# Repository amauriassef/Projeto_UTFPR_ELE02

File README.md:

- [1. Projeto UTFPR ELE02](#1-Projeto-UTFPR-ELE02)
   * [1.1 Universidade Tecnológica Federal do Paraná](#11-Universidade-Tecnológica-Federal-do-Paraná)
   * [1.2 Título](#12-Título)
   * [1.3 Descrição](#13-Descrição)
   * [1.4 Equipe](#14-Equipe)
   * [1.5 Documentação](#15-Documentação)
     + [1.5.1 Características](#151-Características)
     + [1.5.2 Versão do projeto](#152-Versão-do-projeto)
     + [1.5.3 Histórico de versão](#153-Histórico-de-versão)
     + [1.5.4 Informações para fabricação da placa](#154-Informações-para-fabricação-da-placa)
   * [1.6 Pinagem do kit](#16-Pinagem-do-kit)
     + [1.6.1 Descrição dos sinais da placa MICROTB_UTFPR](#161-Descrição-dos-sinais-da-placa-MICROTB_UTFPR)
     + [1.6.2 Descrição dos sinais por funcionalidade](#162-Descrição-dos-sinais-por-funcionalidade) 
        + [1.6.2.1 LEDs](#1621-LEDs) 
        + [1.6.2.2 Chaves push-button](#1622-Chaves-push-button) 
        + [1.6.2.3 Displays de 7 segmentos multiplexados](#1623-Displays-de-7-segmentos-multiplexados) 
        + [1.6.2.4 Display LCD 16x2](#1624-Display-LCD-16x2)
        + [1.6.2.5 Motor de passo e servomotor](#1625-Motor-de-passo-e-servomotor)
        + [1.6.2.6 Módulo sensor de ultrassom HC-04](#1626-Módulo-sensor-de-ultrassom-HC-04)
        + [1.6.2.7 Módulo Bluetooth HC-05 ou HC-06](#1627-Módulo-Bluetooth-HC-05-ou-HC-06)
        + [1.6.2.8 Módulo WiFi ESP8266](#1628-Módulo-WiFi-ESP8266)
        + [1.6.2.9 Módulo I2C sensor de pressão BMP280](#1629-Módulo-I2C-sensor-de-pressão-BMP280)
        + [1.6.2.10 Sinais analógicos](#16210-Sinais-analógicos)
        + [1.6.2.11 Jumpers](#16211-Jumpers)
        + [1.6.2.12 Conectores](#16212-Conectores)
        + [1.6.2.13 Sinais não conectados da placa Tiva LaunchPad](#16213-Sinais-não-conectados-da-placa-Tiva-LaunchPad)
        + [1.6.2.14 Sinais não conectados da placa Blue Pill](#16214-Sinais-não-conectados-da-placa-Blue-Pill)
- [2. Links com informações sobre as placas de avaliação compatíveis](#2-Links-com-informações-sobre-as-placas-de-avaliação-compatíveis)
   * [2.1 Placa TIVA C Series TM4C123G LaunchPad](#21-placa-TIVA-C-Series-TM4C123G-LaunchPad)
     + [2.1.1 Links do professor Jonathan W Valvano](#211-Links-do-professor-Jonathan-W-Valvano)
   * [2.2 Placa Blue Pill](#22-placa-Blue-Pill)
   * [2.3 Placa Black Pill](#23-placa-Black-Pill)
- [3. Site para download do software Eagle](#3-Site-para-download-do-software-Eagle)
- [4. Site do projeto](#4-Site-do-projeto)  
- [5. Como citar este trabalho](#5-Como-citar-este-trabalho)  
- [6. Informação de licença](#6-Informação-de-licença)  

# 1. Projeto UTFPR ELE02 

## 1.1 Universidade Tecnológica Federal do Paraná

* Departamento Acadêmico de Eletrotécnica (DAELT) - Campus Curitiba
* Departamento Acadêmico de Eletrônica (DAELN) - Campus Curitiba
* Departamento de Eletrônica (DAELE) - Campus Ponta Grossa
* Link: http://www.utfpr.edu.br/

## 1.2 Título 

Desenvolvimento de um kit microcontrolado de baixo custo para apoio ao ensino remoto - Projeto ELE02 
 
## 1.3 Descrição 

Projeto do circuito esquemático e *layout* da placa de circuito impresso (PCB) **MICROTB_UTFPR** utilizando o software [Eagle 9.6.2](https://www.autodesk.com/products/eagle/). A placa **MICROTB_UTFPR** permite conexão com a placa TIVA™ C Series TM4C123G LaunchPad ou Blue-Pill para aplicações de Sistemas Microcontrolados envolvendo automação, controle e IoT, entre outras.

Projeto aprovado no [Edital 37/2020 PROGRAD – UTFPR – Área temática de Sistemas Microcontrolados](http://portal.utfpr.edu.br/editais/graduacao-e-educacao-profissional/reitoria/edital-37-2020-prograd) como apoio no desenvolvimento dos Recursos Educacionais Abertos (REA).

Para fins do Edital 37/2020, entende-se que Recursos Educacionais Abertos (REA) “são materiais de aprendizado, ensino e pesquisa em qualquer formato e mídia de domínio público ou com direitos autorais liberados sob uma licença aberta, que permitem acesso, reutilização sem custo, adaptação e redistribuição gratuita” [(UNESCO, 2019)](http://www.unesco.org/new/fileadmin/MULTIMEDIA/HQ/CI/CI/pdf/publications/oer_guidelines_pt.pdf).

## 1.4 Equipe 
 
* Amauri Amorin Assef – Coordenador – http://lattes.cnpq.br/0720172921923496
* Guilherme Luiz Moritz – Colaborador – http://lattes.cnpq.br/0736175449254807
* Delvanei Gomes Bandeira Junior – Colaborador – http://lattes.cnpq.br/2233204054325472
* Guilherme de Santi Peron – Colaborador –  http://lattes.cnpq.br/7845448730478685
* Maurício dos Santos Kaster – Colaborador – http://lattes.cnpq.br/5494434934031784
* Murilo Paulo de Oliveira – Bolsista – http://lattes.cnpq.br/1578999659029568
* Cáled Tarique Pereira – Voluntário – http://lattes.cnpq.br/5596843081337675
 
## 1.5 Documentação

* [**BOM_MICROTB**](/BOM_MICROTB) - Lista de material (*bill of material*) da placa MICROTB_UTFPR.
* [**CAD_EAGLE_9_6_2_MICROTB**](/CAD_EAGLE_9_6_2_MICROTB) - Projeto do circuito esquemático e *layout* da placa MICROTB_UTFPR.
* [**LIB_MICROTB**](/LIB_MICROTB) - Biblioteca com os componentes do circuito esquemático e placa MICROTB_UTFPR.
* [**PDF_MICROTB**](/PDF_MICROTB) - Arquivos em formato PDF para visualização do circuito esquemático e projeto da placa.

Obs: após abrir o arquivo da placa (board) no software Autodesk Eagle versão 9.6.2 (© 2020 Autodesk, Inc.), clicar em **Ratsnest** para mostrar os planos de GND dos layers *top* e *bottom*.

### 1.5.1 Características

* Permite conexão com as placas TIVA™ C Series TM4C123G LaunchPad e Blue Pill
* 2 displays de 7 segmentos tipo catodo comum multiplexados
* 8 LEDs para controle lógico visual
* Sensor de temperatura LM35
* Potenciômetro para leitura analógica
* Driver ponte-H dupla L293D para controle de motor de passo e CC
* Conector para módulo WiFi ESP8266
* Conector para módulo Bluetooth HC-05/06
* Conector para controle de micro servomotor de 3 fios com sinal PWM
* Conector para módulo sensor ultrassônico HC-04
* Conector para módulo sensor de sensor de pressão BMP280
* Display alfanumérico LCD 16x2 no modo de 4 bits
* Alimentação pela USB ou fonte externa de 9 V/1 A com conector do tipo P4 (2,5 x 5,5 mm)

### 1.5.2 Versão do projeto

**MICROTB_UTFPR V1.0** - Versão inicial do projeto

### 1.5.3 Histórico de versão 

**V1.0** - Versão inicial da placa MICROTB_UTFPR 

### 1.5.4 Informações para fabricação da placa

* Material: Dupla face FR4
* Dimensão da placa: 100 x 80 (mm2)
* Espessura da PCI: 1,60 mm
* Acabamento Superficial: HAL (Sn/Pb)
* Espessura final do cobre externo (Base + Plating): 1.0oz
* Cor da máscara de solda (top): Verde
* Cor da máscara de componentes (top): Branca
* Menor pista: 0,28 mm (11 mil)
* Menor isolação: 0,305 mm (12 mil)

## 1.6 Pinagem do kit

### 1.6.1. Descrição dos sinais da placa MICROTB_UTFPR

|Conector TIVA|	Pino do conector M1 (Tiva)|	Sinal Tiva|	Pino do conector M2 (Blue Pill)|	Sinal Blue Pill|	Sinal Black Pill |Nome do sinal final|	Interface  |	Direção    |
|:---:        |:---:                      |:---:      |:---:                           |:---:            |:---:              |:---:              |:---:        |:---:        |
|J1-1	        |1                          |	3,3 V     |	18, 21                         |	3,3 V          |	3,3 V            |	+3V3(TB)         |	Alimentação|	Alimentação|
|J1-2         |3                          |	PB5       |	10                             |	PA5            |	PA6              |	PB5_PA5          |	LED6, SEG_F e LCD_D5       | OUT    |  
|J1-3       	|5	                        |PB0	      |5	                             |PA0	|NRST	|PB0_PA0	|LED1 e SEG_A|	OUT/NC|
|J1-4	|7	|PB1	|6	|PA1	|PA0  |PB1_PA1	|LED2 e SEG_B|	OUT|
|J1-5	|9	|PE4	|16	|PB11	|PB2 |PE4_PB11	|ESP_TX, BLUETOOTH_TX e BMP280	|IN|
|J1-6	|11	|PE5	|15	|PB10	|PB1 |PE5_PB10	|ESP_RX, BLUETOOTH_RX e BMP280	|OUT|
|J1-7	|13	|PB4	|6	|PA4 |PA3	|PB4_PA4	|LED5, SEG_E e LCD_D4	|OUT|
|J1-8	|15	|PA5	|34	|PA10 |PA10	|PA5_PA10	|EN_DISP1	|OUT|
|J1-9	|17	|PA6	|31	|PA15 |PA15	|PA6_PA15	|EN_DISP2	|OUT|
|J1-10	|19	|PA7| PA6|	-|	-	|	-	|-|	-	|NC|
|J2-1	|22	|GND	|19, 22|	GND	|	GND |GND	|Alimentação	|Alimentação|
|J2-2	|24	|PB2	|7	|PA2	|PA1 |PB2_PA2	|LED3 e SEG_C|	OUT|
|J2-3	|26	|PE0	|29	|PB4	|PB4 |PE0_PB4	|ESP_GPIO02	|IN/OUT|
|J2-4	|28	|PF0	|24	|PB9	|PB9 |PF0_PB9	|SW2	|IN|
|J2-5	|30	|RESET	|-	|-	 |-	|-	|-	|NC
|J2-6	|32	|PB7/PD1	|12	|PA7	|PA6 |PB7_PA7	|LED8, SEG_DP e LCD_D7	|OUT|
|J2-7	|34	|PB6/PD0	|11	|PA6	|PA5 |PB6_PA6	|LED7, SEG_G e LCD_D6	|OUT|
|J2-8	|36	|PA4	|28	|PB5	|PB5 |PA4_PB5	|EN_LEDS	|OUT|
|J2-9	|38	|PA3	|40	|PB12	|PB12 |PA3_PB12	|LCD_EN	|OUT|
|J2-10	|40	|PA2	|39	|PB13	|PB13 |PA2_PB13	|LCD_RS	|OUT|
|J3-1	|2	|5,0 V	|23	|5,0 V	|5,0 V |+5V(TB)	|Alimentação	|Alimentação|
|J3-2	|4	|GND	|19, 22	|GND	|GND |GND	|Alimentação	|Alimentação|
|J3-3	|6	|PD0/PB6	|-	|-	|-	|-	|-	|NC|
|J3-4	|8	|PD1/PB7	|-	|-	|-	|-	|-	|NC|
|J3-5	|10	|PD2	|36	|PA8	|PA8 |PD2_PA8	|L293D_M3	|OUT|
|J3-6	|12	|PD3	|35	|PA9	|PA9 |PD3_PA9	|L293D_M4	|OUT|
|J3-7	|14	|PE1	|30	|PB3	|PB3 |PE1_PB3	|ESP_RST	| OUT|
|J3-8	|16	|PE2	|14	|PB1	|PB0 |PE2_PB1	|LM35	|IN (ADC)|
|J3-9	|18	|PE3	|13	|PB0	|PA7 |PE3_PB0	|Trimpot	|IN (ADC)|
|J3-10	|20	|PF1	|2	|PC13	|PC13 |PF1_PC13	|US_TRIGGER	|OUT|
|J4-1	|21	|PF2	|-	|-	|-	|-	|NC|
|J4-2	|23	|PF3	|-	|-	|-	|-	|NC|
|J4-3	|25	|PB3	|8	|PA3	|PA2 |PB3_PA3	|LED4 e SEG_D	|OUT|
|J4-4	|27	|PC4	|27|	PB6	|	PB6 |PC4_PB6	|US_ECO	|IN|
|J4-5	|29	|PC5	|26	|PB7	|PB7 |PC5_PB7	|SERVO e L293D_EN	|OUT (PWM)|
|J4-6	|31	|PC6	|38	|PB14 |PB14	|PC6_PB14	|L293D_M1	|OUT|
|J4-7	|33	|PC7	|37	|PB15	|PB15 |PC7_PB15	|L293D_M2	|OUT|
|J4-8	|35	|PD6	|-	|-	|-	|-	|-	|NC|
|J4-9	|37	|PD7	|-	|-	|-	|-	|-	|NC|
|J4-10	|39	|PF4	|25	|PB8	|PB8 |PF4_PB8	|SW1	|IN|

NC - não conectado. 

### 1.6.2. Descrição dos sinais por funcionalidade

#### 1.6.2.1 LEDs

|Conector TIVA|	Pino do conector M1 (Tiva)|	Sinal Tiva|	Pino do conector M2 (Blue Pill)|	Sinal Blue Pill|	Sinal Black Pill | Nome do sinal final|	Interface  |	Direção    |
|:---:        |:---:                      |:---:      |:---:                          |:---:          |:---:           |:---:      |:---:        |:---:        |
|J2-8	|36	|PA4	|28	|PB5	|PB5 |PA4_PB5	|EN_LEDS	|OUT|
|J1-3	|5	|PB0	|5	|PA0	|NRST |PB0_PA0	|LED1	|OUT/NC|
|J1-4	|7	|PB1	|6	|PA1	|PA0 |PB1_PA1	|LED2	|OUT|
|J2-2	|24	|PB2	|7	|PA2	|PA1 |PB2_PA2	|LED3	|OUT|
|J4-3	|25	|PB3	|8	|PA3	|PA2 |PB3_PA3	|LED4	|OUT|
|J1-7	|13	|PB4	|6	|PA4	|PA3 |PB4_PA4	|LED5	|OUT|
|J1-2	|3	|PB5	|10	|PA5	|PA4 |PB5_PA5	|LED6	|OUT|
|J2-7	|34	|PB6/PD0	|11	|PA6	|PA5 |PB6_PA6	|LED7	|OUT|
|J2-6	|32	|PB7/PD1	|12	|PA7	|PA6 |PB7_PA7	|LED8	|OUT|

#### 1.6.2.2 Chaves push-button

|Conector TIVA|	Pino do conector M1 (Tiva)|	Sinal Tiva|	Pino do conector M2 (Blue Pill)|	Sinal Blue Pill|	Sinal Black Pill | Nome do sinal final|	Interface  |	Direção    |
|:---:        |:---:                      |:---:      |:---:                          |:---:          |:---:           |:---:      |:---:        |:---:        |
|J4-10	      |39	                         |PF4	         |25	                              |PB8	            |PB8               |PF4_PB8	             |SW1	         |IN         |
|J2-4	|28	|PF0	|24	|PB9	|PB9 |PF0_PB9	|SW2	|IN|

#### 1.6.2.3 Displays de 7 segmentos multiplexados
 
|Conector TIVA|	Pino do conector M1 (Tiva)|	Sinal Tiva|	Pino do conector M2 (Blue Pill)|	Sinal Blue Pill|	Sinal Black Pill | Nome do sinal final|	Interface  |	Direção    |
|:---:        |:---:                      |:---:      |:---:                          |:---:          |:---:           |:---:      |:---:        |:---:        |
|J1-8	|15	|PA5	|34	|PA10	|PA10 |PA5_PA10	|EN_DISP1	|OUT|
|J1-9	|17	|PA6	|31	|PA15 |PA15	|PA6_PA15	|EN_DISP2	|OUT|
|J1-3	|5	|PB0	|5	|PA0	|NRST |PB0_PA0	|SEG_A	|OUT/NC|
|J1-4	|7	|PB1	|6	|PA1	|PA0 |PB1_PA1	|SEG_B	|OUT|
|J2-2	|24	|PB2	|7	|PA2	|PA1 |PB2_PA2	|SEG_C	|OUT|
|J4-3	|25	|PB3	|8	|PA3	|PA2 |PB3_PA3	|SEG_D	|OUT|
|J1-7	|13	|PB4	|6	|PA4	|PA3 |PB4_PA4	|SEG_E	|OUT|
|J1-2	|3	|PB5	|10	|PA5	|PA4 |PB5_PA5	|SEG_F	|OUT|
|J2-7	|34	|PB6/PD0	|11	|PA6	|PA5 |PB6_PA6	|SEG_G	|OUT|
|J2-6	|32	|PB7/PD1	|12	|PA7	|PA6 |PB7_PA7	|SEG_DP	|OUT|

#### 1.6.2.4 Display LCD 16x2

|Conector TIVA|	Pino do conector M1 (Tiva)|	Sinal Tiva|	Pino do conector M2 (Blue Pill)|	Sinal Blue Pill|	Sinal Black Pill | Nome do sinal final|	Interface  |	Direção    |
|:---:        |:---:                      |:---:      |:---:                          |:---:          |:---:           |:---:      |:---:        |:---:        |
|J2-9	|38	|PA3	|40	|PB12	|PB12 |PA3_PB12	|LCD_EN	|OUT|
|J2-10	|40	|PA2	|39	|PB13	|PB13 |PA2_PB13	|LCD_RS	|OUT|
|J1-7	|13	|PB4	|6	|PA4	|PA3 |PB4_PA4	|LCD_D4	|OUT|
|J1-2	|3	|PB5	|10	|PA5	|PA4 |PB5_PA5	|LCD_D5	|OUT|
|J2-7	|34	|PB6/PD0	|11	|PA6	|PA5 |PB6_PA6	|LCD_D6	|OUT|
|J2-6	|32	|PB7/PD1	|12	|PA7	|PA6 |PB7_PA7	|LCD_D7	|OUT|

#### 1.6.2.5 Motor de passo e servomotor

|Conector TIVA|	Pino do conector M1 (Tiva)|	Sinal Tiva|	Pino do conector M2 (Blue Pill)|	Sinal Blue Pill|	Sinal Black Pill | Nome do sinal final|	Interface  |	Direção    |
|:---:        |:---:                      |:---:      |:---:                          |:---:          |:---:           |:---:      |:---:        |:---:        |
|J4-5	|29	|PC5	|26	|PB7	|PB7 |PC5_PB7	|SERVO e L293D_EN	|OUT (PWM)|
|J4-6	|31	|PC6	|38	|PB14	|PB14 |PC6_PB14	|L293D_M1	|OUT|
|J4-7	|33	|PC7	|37	|PB15 |PB15	|PC7_PB15	|L293D_M2	|OUT|
|J3-5	|10	|PD2	|36	|PA8	|PA8	|PD2_PA8	|L293D_M3	|OUT|
|J3-6	|12	|PD3	|35	|PA9	|PA9	|PD3_PA9	|L293D_M4	|OUT|

#### 1.6.2.6 Módulo sensor de ultrassom HC-04

|Conector TIVA|	Pino do conector M1 (Tiva)|	Sinal Tiva|	Pino do conector M2 (Blue Pill)|	Sinal Blue Pill|	Sinal Black Pill | Nome do sinal final|	Interface  |	Direção    |
|:---:        |:---:                      |:---:      |:---:                          |:---:          |:---:           |:---:      |:---:        |:---:        |
|J3-10	|20	|PF1	|2	|PC13	|PC13 |PF1_PC13	|US_TRIGGER	|OUT|
|J4-4	|27	|PC4	|27	|PB6	|PB6 |PC4_PB6	|US_ECO	|IN|

#### 1.6.2.7 Módulo Bluetooth HC-05 ou HC-06

|Conector TIVA|	Pino do conector M1 (Tiva)|	Sinal Tiva|	Pino do conector M2 (Blue Pill)|	Sinal Blue Pill|	Sinal Black Pill | Nome do sinal final|	Interface  |	Direção    |
|:---:        |:---:                      |:---:      |:---:                          |:---:          |:---:           |:---:      |:---:        |:---:        |
|J1-5	|9	|PE4	|16	|PB11	|PB2 |PE4_PB11	|BLUETOOTH_TX	|IN|
|J1-6	|11	|PE5	|15	|PB10	|PB1 |PE5_PB10	|BLUETOOTH_RX	|OUT|

#### 1.6.2.8 Módulo WiFi ESP8266

|Conector TIVA|	Pino do conector M1 (Tiva)|	Sinal Tiva|	Pino do conector M2 (Blue Pill)|	Sinal Blue Pill|	Sinal Black Pill | Nome do sinal final|	Interface  |	Direção    |
|:---:        |:---:                      |:---:      |:---:                          |:---:          |:---:           |:---:      |:---:        |:---:        |
|J2-3	|26	|PE0	|29	|PB4	|PB4	|PE0_PB4	|ESP_GPIO02	|OUT|
|J3-7	|14	|PE1	|30	|PB3	|PB3	|PE1_PB3	|ESP_RST	|OUT|
|J1-5	|9	|PE4	|16	|PB11	|PB2	|PE4_PB11	|ESP_TX	|IN|
|J1-6	|11	|PE5	|15	|PB10	|PB1 |PE5_PB10	|ESP_RX	|OUT|

#### 1.6.2.9 Módulo I2C sensor de pressão BMP280

|Conector TIVA|	Pino do conector M1 (Tiva)|	Sinal Tiva|	Pino do conector M2 (Blue Pill)|	Sinal Blue Pill|	Sinal Black Pill | Nome do sinal final|	Interface  |	Direção    |
|:---:        |:---:                      |:---:      |:---:                          |:---:          |:---:           |:---:      |:---:        |:---:        |
|J1-5	|9	|PE4	|16	|PB11	|PB2 |PE4_PB11	|BMP280_SCL	|IN
|J1-6	|11	|PE5	|15	|PB10	|PB1 |PE5_PB10	|BMP280_SDA	|OUT

**Observação**: Inverter os sinais PE4_PB11 e PE5_PB10 para funcionamento do BMP280 com a placa Blue-Pill (PB10 – SCL e PB11 – SDA)

#### 1.6.2.10 Sinais analógicos

|Conector TIVA|	Pino do conector M1 (Tiva)|	Sinal Tiva|	Pino do conector M2 (Blue Pill)|	Sinal Blue Pill|	Sinal Black Pill | Nome do sinal final|	Interface  |	Direção    |
|:---:        |:---:                      |:---:      |:---:                          |:---:          |:---:           |:---:      |:---:        |:---:        |
|J3-8	|16	|PE2	|14	|PB1	|PB0 |PE2_PB1	|LM35	|IN (ADC)|
|J3-9	|18	|PE3	|13	|PB0	|PA7 |PE3_PB0	|Trimpot	|IN (ADC)|

#### 1.6.2.11 Jumpers

|Jumper|	Pinos |	Descrição|
|:---: |:---:   |:---:     |
|JP1	|1-2	|Alimentação pela USB (padrão)|
|JP1	|2-3	|Alimentação por fonte externa| 
|JP2	|1-2	|Utilizado para teste da placa MICROTB_UTFPR |
|JP2	|2-3	|Alimentação pelo regulador de 3,3 V da placa (padrão)|

#### 1.6.2.12 Conectores

|Posição	|Conexão|
|:---:    |:---:  |
|LCD1	|LCD 16x2|
|M1	|Placa Tiva LaunchPad|
|M2	|Placa Blue Pill|
|P1	|Servomotor|
|P2	|Motor de passo unipolar ou até dois motores CC|
|P3	|ESP8266|
|P4	|Módulo Bluetooth HC-05/HC-06|
|P5	|Módulo de pressão BPM280|
|P6	|Módulo sensor ultrassônico HC-04|
|U1	|Entrada da alimentação de 9 V|

#### 1.6.2.13 Sinais não conectados da placa Tiva LaunchPad

|Pino do conector M1	|Sinal Tiva	|Descrição|
|:---:                |:---:          |:---:    |
|19 (J1-10)	|PA7	|I/O|
|6 (J3-3)	|PD0	|Conectado por um resistor de 0R no PB6|
|8 (J3-4)	|PD1	|Conectado por um resistor de 0R no PB7|
|21 (J4-1)	|PF2	|LED Azul da placa Tiva|
|23 (J4-2)	|PF3	|LED Verde da placa Tiva|
|35 (J4-8)	|PD6	|I/O|
|37 (J4-9)	|PD7	|I/O NMI|
|30 (J2-5)	|RESET	|RESET|

#### 1.6.2.14 Sinais não conectados da placa Blue Pill

|Pino do conector M2	|Sinal Blue Pill	|Descrição|
|:---:                |:---:          |:---:    |
|3	|PC14	|OSC32IN|
|4	|PC15	|OSC32OUT|
|17	|NRST	|RESET BUTTON|
|20	|\*GND	|GND|
|32	|PA12	|USB+|
|33	|PA11	|USB+|

\*Sinal não conectado para compatibilidade com a placa BlackPill.

NRST - cortar o pino NRST

#### 1.6.2.15 Sinais não conectados da placa Black Pill

|Pino do conector M2	|Sinal Black Pill	|Descrição|
|:---:                |:---:          |:---:    |
|3	|PC14	|OSC32IN|
|4	|PC15	|OSC32OUT|
|5	|NRST	|RESET BUTTON|
|20	|+5V	|+5V|
|32	|PA12	|USB+|
|33	|PA11	|USB+|

NRST - cortar o pino NRST

# 2. Links com informações sobre as placas de avaliação compatíveis

## 2.1 Placa TIVA C Series TM4C123G LaunchPad

* [Página WEB da Texas Instruments](https://www.ti.com)
* [Tiva™ C Series TM4C123G LaunchPad Evaluation Board User’s Guide](https://www.ti.com/lit/ug/spmu296/spmu296.pdf)
* [Tiva™ TM4C123GH6PM Microcontroller Datasheet](https://www.ti.com/lit/ds/spms376e/spms376e.pdf)
* [Mini Curso - Getting Started with the TIVA™ C Series TM4C123G LaunchPad](http://software-dl.ti.com/trainingTTO/trainingTTO_public_sw/GSW-TM4C123G-LaunchPad/TM4C123G_LaunchPad_Workshop_Workbook.pdf)
* [Site ARM® Cortex®-M4F Based MCU TM4C123G LaunchPad™ Evaluation Kit](https://www.ti.com/tool/EK-TM4C123GXL)
* [TivaWare™ Peripheral Driver Library User's Guide](https://www.ti.com/lit/ug/spmu298d/spmu298d.pdf)
* [Drivers para o TM4C123 - TivaWare for C Series Software (Complete)](https://www.ti.com/tool/download/SW-TM4C)
* [e-Store Texas Instruments para o Launchpad](https://www.ti.com/store/ti/en/p/product/?p=EK-TM4C123GXL)

### 2.1.1 Links do professor Jonathan W Valvano

* [Página pessoal do professor Jonathan W. Valvano - Univerdidade do Texas em Austin](http://users.ece.utexas.edu/~valvano/)
* [Página do curso Embedded Systems - Shape the World: Microcontroller I/O](https://www.edx.org/course/embedded-systems-shape-the-world-microcontroller-i)
* [Página do curso Embedded Systems - Shape the World: Multi Threaded I/O](https://www.edx.org/course/embedded-systems-shape-the-world-multi-threaded-in)
* [Página do curso Embedded System no EDx (kit e softwares)](http://edx-org-utaustinx.s3.amazonaws.com/UT601x/index.html)

## 2.2 Placa Blue Pill

* [Página WEB da STMicroelectronics](https://www.st.com/content/st_com/en.html)
* [Canal da STMicroelectronics no Youtube](https://www.youtube.com/c/stmicroelectronics/videos)
* [STM32world.com wiki](https://stm32world.com/wiki/Main_Page)
* [ST Flasher](https://github.com/stlink-org/stlink/releases)
* [Blue Pill - Informações Gerais](https://stm32-base.org/boards/STM32F103C8T6-Blue-Pill)
* [Blue Pill - Circuito esquemático (easyEDA)](https://easyeda.com/r3bers/STM32F103C8T6-Test-Board)
* [Blue Pill - Datasheet do STM32F103C8](https://www.st.com/resource/en/datasheet/stm32f103c8.pdf)
* [Blue Pill - Reference Manual do STM32F103C8](https://www.st.com/resource/en/reference_manual/cd00171190-stm32f101xx-stm32f102xx-stm32f103xx-stm32f105xx-and-stm32f107xx-advanced-arm-based-32-bit-mcus-stmicroelectronics.pdf)
* [Blue Pill - Documentação da API do STM32F1](https://www.st.com/resource/en/user_manual/dm00154093-description-of-stm32f1-hal-and-lowlayer-drivers-stmicroelectronics.pdf)
* [Página embeddedexpert.io - Exemplos de códigos](https://embeddedexpert.io/)
* [Tutorial de instalação do ambiente de dupuração/programação - Prof. Guilherme L. Moritz](https://drive.google.com/file/d/1uLPW_LXY3d8g-7BL5YjpZ9rex4Q9JGck/view?usp=sharing)
* [Vídeo tutorial de instalação do ambiente de dupuração/programação - Prof. Guilherme L. Moritz](https://youtu.be/wEANQKCs-E4)

## 2.3 Placa BlackPill

* [Blackpill - Pinagem (Zephyr Project) e informações Gerais](https://docs.zephyrproject.org/latest/boards/arm/blackpill_f411ce/doc/index.html)
* [Blackpill - Circuito esquemático](https://stm32-base.org/assets/pdf/boards/original-schematic-STM32F411CEU6_WeAct_Black_Pill_V2.0.pdf)
* [Blackpill - Datasheet do STM32F411RE](https://www.st.com/resource/en/datasheet/stm32f411re.pdf)
* [Blackpill - Reference Manual do STM32F411RE](https://www.st.com/resource/en/reference_manual/dm00119316-stm32f411xc-e-advanced-arm-based-32-bit-mcus-stmicroelectronics.pdf)
* [Blackpill - Documentação da API do STM32F4](https://www.st.com/resource/en/user_manual/dm00105879-description-of-stm32f4-hal-and-ll-drivers-stmicroelectronics.pdf)

# 3. Site para download do software Eagle

* Link: https://www.autodesk.com/products/eagle/free-download

# 4. Site do projeto

O site do projeto foi desenvolvido pelo estudante *Cáled Tarique Pereira* do curso de Engenharia de Controle e Automação da UTFPR Campus Cornélio Procópio.
* Link: https://ele002.wordpress.com/   

# 5. Como citar este trabalho

ASSEF, Amauri Amorin; MORITZ, Guilherme Luiz; BANDEIRA JUNIOR, Delvanei Gomes; PERON, Guilherme de Santi; KASTER, Maurício dos Santos; OLIVEIRA, Murilo Paulo de; PEREIRA, Cáled Tarique. Projeto aberto da placa MICROTB_UTFPR (V1.0) para conexão com as plataformas de avaliação de microcontroladores baseados em ARM Tiva LaunchPad e Blue Pill. Curitiba: UTFPR, 2021. 

# 6. Informação de licença 

Esta obra está licenciada com uma Licença Creative Commons BY-NC-SA 4.0. Esta licença permite que outros remixem, adaptem e criem a partir do trabalho para fins não comerciais, desde que atribuam o devido crédito e que licenciem as novas criações sob termos idênticos. Conteúdos elaborados por terceiros, citados e referenciados nesta obra não são cobertos pela licença. Para ver uma cópia da licença, visite http://creativecommons.org/licenses/by-nc-sa/4.0/

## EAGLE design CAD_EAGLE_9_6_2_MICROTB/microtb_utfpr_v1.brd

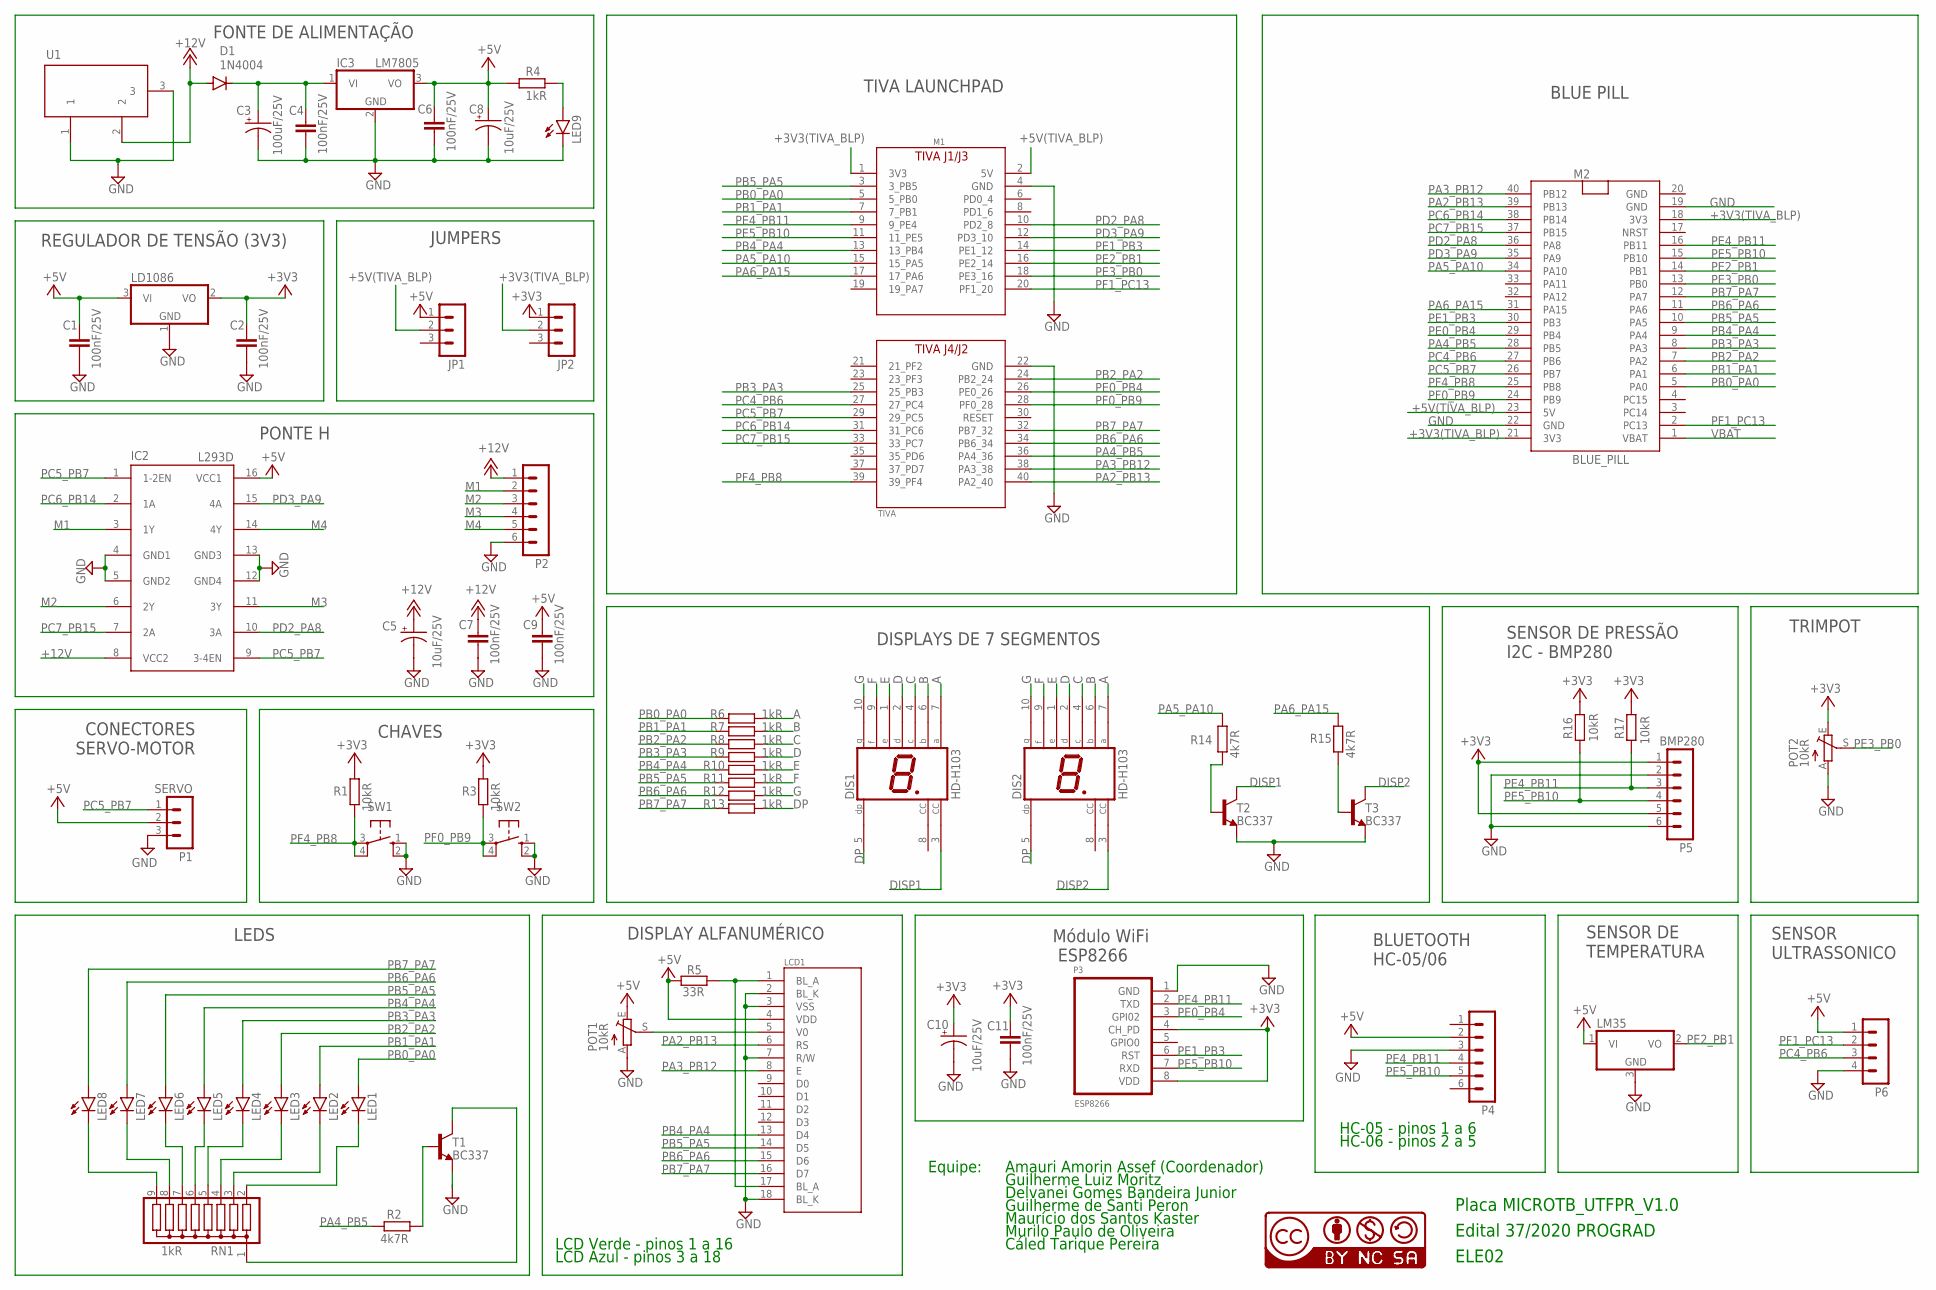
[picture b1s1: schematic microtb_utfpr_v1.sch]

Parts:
C1, C2, C4, C6, C7, C9, C11: 100nF/25V; C2.5-2
C3: 100uF/25V; E2,5-7
C5, C8, C10: 10uF/25V; E2,5-6
D1: 1N4004; DO41-10
DIS1, DIS2: HD-H103; HDSP-M
IC1: LD1086
IC2: L293D; DIL16
IC3: LM7805; TO220V
JP1, JP2: JP; MA03-1
LCD1: DISPLAY_LCDDISPLAY_LCD1; DISPLAY_LCD_BL
LED1, LED2, LED3, LED4, LED5, LED6, LED7, LED8: GREEN; LED3MM
LED9: RED; LED3MM
M1: TIVA
M2: BLUE_PILL
P1: SERVO; MA03-1
P2: Motor; HC_BLUETOOTH
P3: ESP8266
P4: HC05_06; HC_BLUETOOTH
P5: BMP280
P6: HC-04; HS-04
POT1: 10kR; CA6V
POT2: 10kR; CIP20C-4MM
Q1: LM35L05Z; LM35
R1, R3, R16, R17: 10kR; 0204/7
R2, R14, R15: 4k7R; 0204/7
R4, R6, R7, R8, R9, R10, R11, R12, R13: 1kR; 0204/7
R5: 33R; 0204/7
RN1: 1kR; SIL9
SW1, SW2: SW; B3F-10XX
T1, T2, T3: BC337; TO92-CBE
U1: POWERSUPPLY_DC21MMX; POWERSUPPLY_DC-21MM
U$1: CC-NC-BC; CC-NC-BY

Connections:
+3V3: C2.1, C10.+, C11.1, IC1.2 (VO), JP2.1, P3.4 (CH_PD), P3.8 (VDD), P5.1, P5.5, POT2.E, R1.2, R3.2, R16.2, R17.2
+3V3(TIVA_BLP): JP2.2, M1.1 (3V3), M2.18 (3V3), M2.21 (3V3)
+5V: C1.1, C6.1, C8.+, C9.1, IC1.3 (VI), IC2.16 (VCC1), IC3.3 (VO), JP1.1, LCD1.4 (VDD), P1.2, P4.2, P6.1, POT1.E, Q1.1 (VI), R4.1, R5.2
+5V(TIVA_BLP): JP1.2, M1.2 (5V), M2.23 (5V)
+12V: C5.+, C7.1, D1.A, IC2.8 (VCC2), P2.1, U1.2
+V: C3.+, C4.1, D1.C, IC3.1 (VI)
A: DIS1.7 (A), DIS2.7 (A), R6.1
B: DIS1.6 (B), DIS2.6 (B), R7.1
C: DIS1.4 (C), DIS2.4 (C), R8.1
D: DIS1.2 (D), DIS2.2 (D), R9.1
DISP1: DIS1.3 (CC), T2.C
DISP2: DIS2.3 (CC), T3.C
DP: DIS1.5 (DP), DIS2.5 (DP), R13.1
E: DIS1.1 (E), DIS2.1 (E), R10.1
F: DIS1.9 (F), DIS2.9 (F), R11.1
G: DIS1.10 (G), DIS2.10 (G), R12.1
GND: C1.2, C2.2, C3.-, C4.2, C5.-, C6.2, C7.2, C8.-, C9.2, C10.-, C11.2, IC1.1 (GND), IC2.4 (GND1), IC2.5 (GND2), IC2.12 (GND4), IC2.13 (GND3), IC3.2 (GND), LCD1.2 (BL_K), LCD1.3 (VSS), LCD1.7 (R/W), LCD1.18 (BL_K), LED9.K (C), M1.4 (GND), M1.22 (GND), M2.19 (GND), M2.22 (GND), P1.3, P2.6, P3.1 (GND), P4.3, P5.2, P5.6, P6.4, POT1.A, POT2.A, Q1.3 (GND), SW1.1 (S), SW1.2 (S1), SW2.1 (S), SW2.2 (S1), T1.E, T2.E, T3.E, U1.1, U1.3
M1: IC2.3 (1Y), P2.2
M2: IC2.6 (2Y), P2.3
M3: IC2.11 (3Y), P2.4
M4: IC2.14 (4Y), P2.5
unnamed: LED8.K (C), RN1.9
unnamed: R14.1, T2.B
unnamed: R15.1, T3.B
unnamed: LED9.A, R4.2
unnamed: R2.2, T1.B
unnamed: LED7.K (C), RN1.8
unnamed: LED6.K (C), RN1.7
unnamed: LED5.K (C), RN1.6
unnamed: LED4.K (C), RN1.5
unnamed: LED3.K (C), RN1.4
unnamed: LED2.K (C), RN1.3
unnamed: LED1.K (C), RN1.2
unnamed: LCD1.1 (BL_A), LCD1.17 (BL_A), R5.1
unnamed: RN1.1, T1.C
PA2_PB13: LCD1.6 (RS), M1.40 (PA2_40), M2.39 (PB13)
PA3_PB12: LCD1.8 (E), M1.38 (PA3_38), M2.40 (PB12)
PA4_PB5: M1.36 (PA4_36), M2.28 (PB5), R2.1
PA5_PA10: M1.15 (15_PA5), M2.34 (PA10), R14.2
PA6_PA15: M1.17 (17_PA6), M2.31 (PA15), R15.2
PB0_PA0: LED1.A, M1.5 (5_PB0), M2.5 (PA0), R6.2
PB1_PA1: LED2.A, M1.7 (7_PB1), M2.6 (PA1), R7.2
PB2_PA2: LED3.A, M1.24 (PB2_24), M2.7 (PA2), R8.2
PB3_PA3: LED4.A, M1.25 (25_PB3), M2.8 (PA3), R9.2
PB4_PA4: LCD1.13 (D4), LED5.A, M1.13 (13_PB4), M2.9 (PA4), R10.2
PB5_PA5: LCD1.14 (D5), LED6.A, M1.3 (3_PB5), M2.10 (PA5), R11.2
PB6_PA6: LCD1.15 (D6), LED7.A, M1.34 (PB6_34), M2.11 (PA6), R12.2
PB7_PA7: LCD1.16 (D7), LED8.A, M1.32 (PB7_32), M2.12 (PA7), R13.2
PC4_PB6: M1.27 (27_PC4), M2.27 (PB6), P6.3
PC5_PB7: IC2.1 (1-2EN), IC2.9 (3-4EN), M1.29 (29_PC5), M2.26 (PB7), P1.1
PC6_PB14: IC2.2 (1A), M1.31 (31_PC6), M2.38 (PB14)
PC7_PB15: IC2.7 (2A), M1.33 (33_PC7), M2.37 (PB15)
PD2_PA8: IC2.10 (3A), M1.10 (PD2_8), M2.36 (PA8)
PD3_PA9: IC2.15 (4A), M1.12 (PD3_10), M2.35 (PA9)
PE0_PB4: M1.26 (PE0_26), M2.29 (PB4), P3.3 (GPI02)
PE1_PB3: M1.14 (PE1_12), M2.30 (PB3), P3.6 (RST)
PE2_PB1: M1.16 (PE2_14), M2.14 (PB1), Q1.2 (VO)
PE3_PB0: M1.18 (PE3_16), M2.13 (PB0), POT2.S
PE4_PB11: M1.9 (9_PE4), M2.16 (PB11), P3.2 (TXD), P4.4, P5.3, R17.1
PE5_PB10: M1.11 (11_PE5), M2.15 (PB10), P3.7 (RXD), P4.5, P5.4, R16.1
PF0_PB9: M1.28 (PF0_28), M2.24 (PB9), R3.1, SW2.3, SW2.4 (P1)
PF1_PC13: M1.20 (PF1_20), M2.2 (PC13), P6.2
PF4_PB8: M1.39 (39_PF4), M2.25 (PB8), R1.1, SW1.3, SW1.4 (P1)
VBAT: M2.1 (VBAT)
VO: LCD1.5 (V0), POT1.S

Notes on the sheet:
FONTE DE ALIMENTAÇÃO
TIVA LAUNCHPAD
PONTE H
LEDS
DISPLAY ALFANUMÉRICO
DISPLAYS DE 7 SEGMENTOS
BLUETOOTH HC-05/06
SENSOR ULTRASSONICO
SENSOR DE TEMPERATURA
CONECTORES SERVO-MOTOR
SENSOR DE PRESSÃO I2C - BMP280
CHAVES
TRIMPOT
Módulo WiFi ESP8266
REGULADOR DE TENSÃO (3V3)
JUMPERS
BLUE PILL
Placa MICROTB_UTFPR_V1.0
Edital 37/2020 PROGRAD
ELE02
Equipe:
Amauri Amorin Assef (Coordenador)
Guilherme Luiz Moritz
Delvanei Gomes Bandeira Junior
Guilherme de Santi Peron
Maurício dos Santos Kaster
Murilo Paulo de Oliveira
Cáled Tarique Pereira
HC-06 - pinos 2 a 5
HC-05 - pinos 1 a 6
LCD Verde - pinos 1 a 16
LCD Azul - pinos 3 a 18

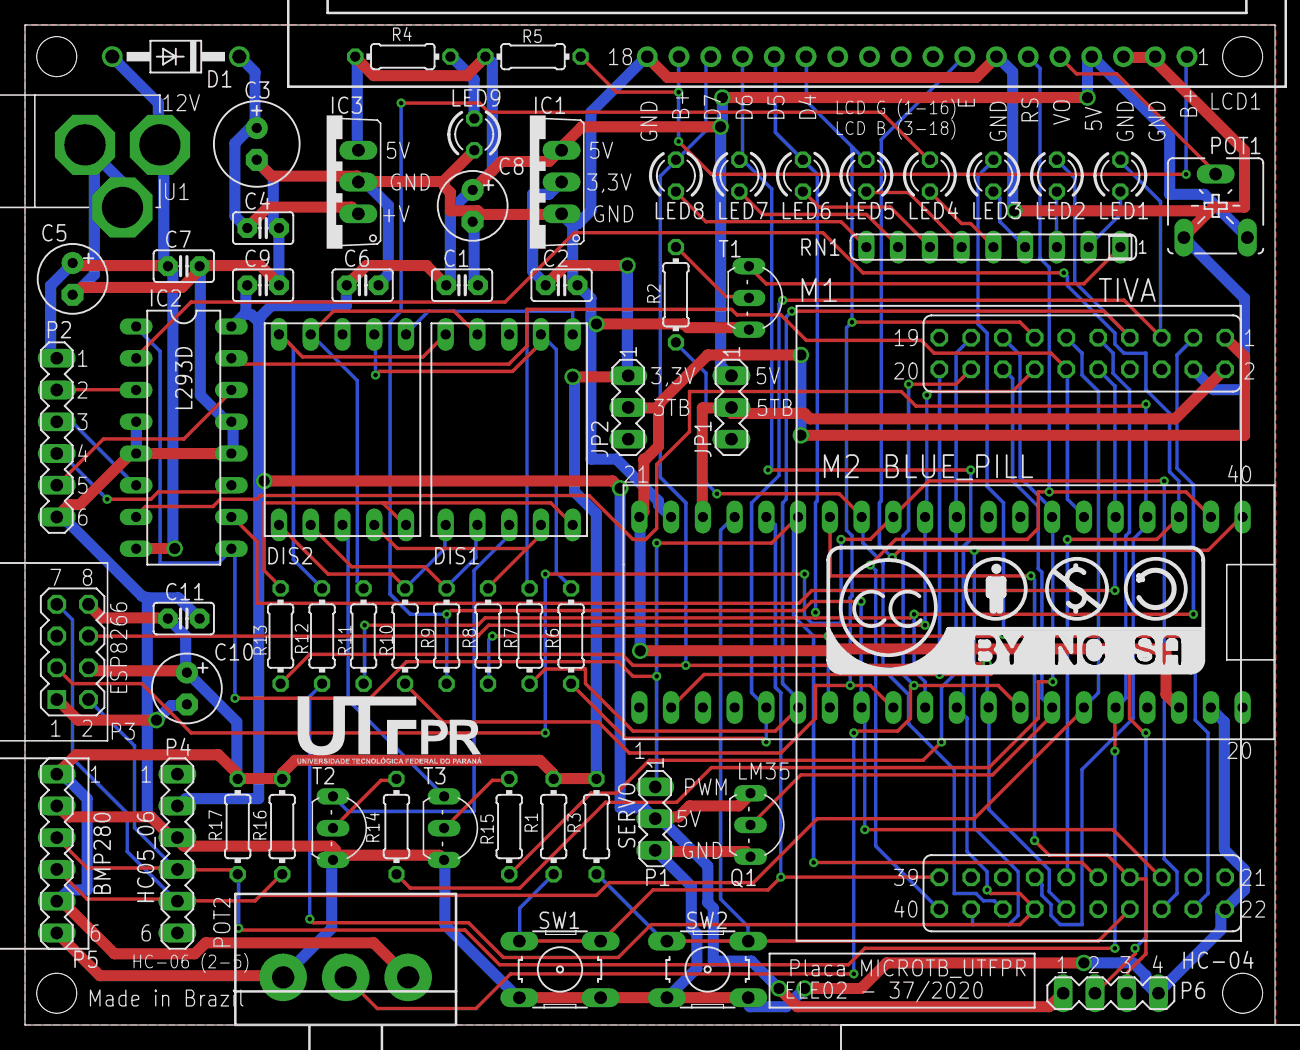
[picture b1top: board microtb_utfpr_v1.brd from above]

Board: 2 copper layers, 100.0 x 80.0 mm, 65 parts (0 on the bottom side), 64 nets.

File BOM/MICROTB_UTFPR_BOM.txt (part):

Partlist exported from C:/Users/n/Desktop/MICROTB_V0/ele02_at.sch at 21/06/2021 17:10

Part Value                   Device                  Package             Description                                         MF MPN      OC_FARNELL OC_NEWARK POPULARITY SPICEPREFIX
C1   100nF/25V               C2.5/2                  C2.5-2              CAPACITOR                                                                            28                    
C2   100nF/25V               C2.5/2                  C2.5-2              CAPACITOR                                                                            28                    
C3   100uF/25V               CAPACITOR-PE2.5-7       E2,5-7              POLARIZED CAPACITOR, American symbol                                                                       
C4   100nF/25V               C2.5/2                  C2.5-2              CAPACITOR                                                                            28                    
C5   10uF/25V                CAPACITOR-PE2.5-6       E2,5-6              POLARIZED CAPACITOR, American symbol                                                                       
C6   100nF/25V               C2.5/2                  C2.5-2              CAPACITOR                                                                            28                    
C7   100nF/25V               C2.5/2                  C2.5-2              CAPACITOR                                                                            28                    
C8   10uF/25V                CAPACITOR-PE2.5-6       E2,5-6              POLARIZED CAPACITOR, American symbol                                                                       
C9   100nF/25V               C2.5/2                  C2.5-2              CAPACITOR                                                                            28                    
C10  10uF/25V                CAPACITOR-PE2.5-6       E2,5-6              POLARIZED CAPACITOR, American symbol                                                                       
C11  100nF/25V               C2.5/2                  C2.5-2              CAPACITOR                                                                            28                    
D1   1N4004                  1N4004                  DO41-10             DIODE                                                                                82                    
DIS1 HD-H103                 HD-H103                 HDSP-M              LED DISPLAY                                                     unknown    unknown   1                     
DIS2 HD-H103                 HD-H103                 HDSP-M              LED DISPLAY                                                     unknown    unknown   1                     
IC1  LD1086                  LD108605TV              LD1086              Positive VOLTAGE REGULATOR                                                           57                    
IC2  L293D                   L293D                   DIL16               PUSH-PULL 4 CHANNEL DRIVER                             L293D    9589619    56P8249   16                    
IC3  LM7805                  786TV                   TO220V              Positive VOLTAGE REGULATOR                                                           0                     
JP1  JP                      JUMP                    MA03-1              PIN HEADER                                                      unknown    unknown   48                    
JP2  JP                      JUMP                    MA03-1              PIN HEADER                                                      unknown    unknown   48                    
LCD1 DISPLAY_LCDDISPLAY_LCD1 DISPLAY_LCDDISPLAY_LCD1 DISPLAY_LCD_BL      LCD 16X2                                                                                                   
LED1 GREEN                   LED3MM                  LED3MM              LED                                                                                  97                    
LED2 GREEN                   LED3MM                  LED3MM              LED                                                                                  97                    
LED3 GREEN                   LED3MM                  LED3MM              LED                                                                                  97                    
LED4 GREEN                   LED3MM                  LED3MM              LED                                                                                  97                    
LED5 GREEN                   LED3MM                  LED3MM              LED                                                                                  97                    
LED6 GREEN                   LED3MM                  LED3MM              LED                                                                                  97                    
LED7 GREEN                   LED3MM                  LED3MM              LED                                                                                  97                    
LED8 GREEN                   LED3MM                  LED3MM              LED                                                                                  97                    
LED9 RED                     LED3MM                  LED3MM              LED                                                                                  97                    
M1   TIVA                    TIVA                    TIVA                Conectores da placa Tiva Launch Pad                                                                        
M2   BLUE_PILL               BLUE_PILL               BLUE_PILL           Placa Blue Pill STM 32                                                                                     
P1   SERVO                   CON3                    MA03-1              PIN HEADER                                                      unknown    unknown   48                    
P2   Motor                   MA06-1                  HC_BLUETOOTH        PIN HEADER                                                      unknown    unknown   28                    
P3   ESP8266                 ESP8266                 ESP8266             ESP8266 IoT                                                                                                
P4   HC05_06                 HC05_06                 HC_BLUETOOTH                                                                                                                   
P5   BMP280                  BMP280                  BMP280              BMP280 Sensor                                                                                              
P6   HC-04                   HC-SR04US               HS-04               HC-SR04 Sensor de US                                            unknown    unknown   41                    
POT1 10kR                    TRIM_EU-ELE02CA6V       CA6V                POTENTIOMETER                                                                        10                    
POT2 10kR                    TRIM_EU-CIP20C-4MM      CIP20C-4MM          POTENTIOMETER                                                                        0                     
Q1   LM35L05Z                LM35L05Z                LM35                Positive VOLTAGE REGULATOR                                                           12                    
R1     10kR                  R-EU_0204/7             0204/7              RESISTOR, European symbol                                                            79         R          
R2   4k7R                    R-EU_0204/7             0204/7              RESISTOR, European symbol                                                            79         R          
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
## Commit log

2021-06-22 Create Figuras
2021-06-22 Create licenca
2021-06-22 Update licenca

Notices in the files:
README.md:
Esta obra está licenciada com uma Licença Creative Commons BY-NC-SA 4.0.
parts and their libraries:
cc-by-nc-sa: All hardware is licensed under the Creative Commons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
